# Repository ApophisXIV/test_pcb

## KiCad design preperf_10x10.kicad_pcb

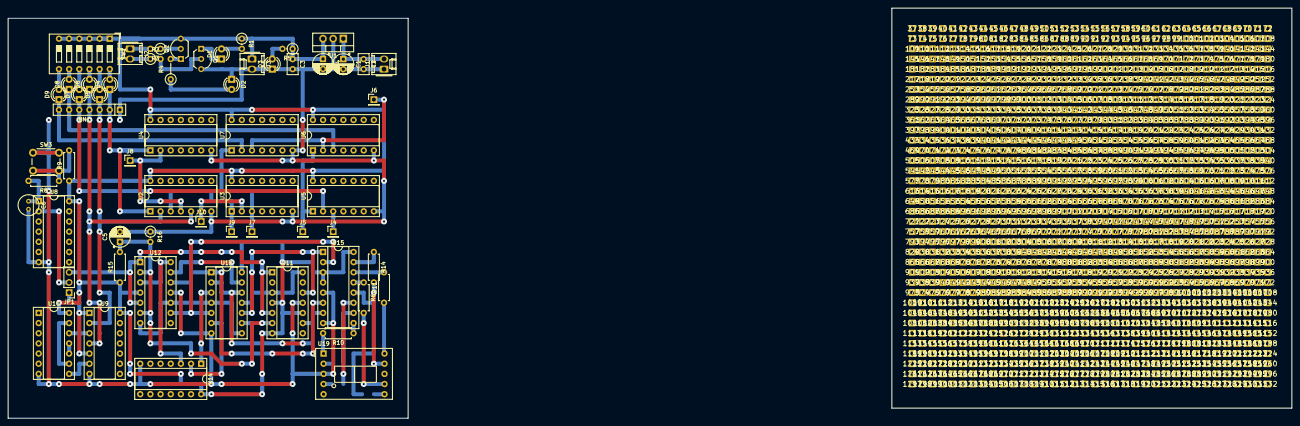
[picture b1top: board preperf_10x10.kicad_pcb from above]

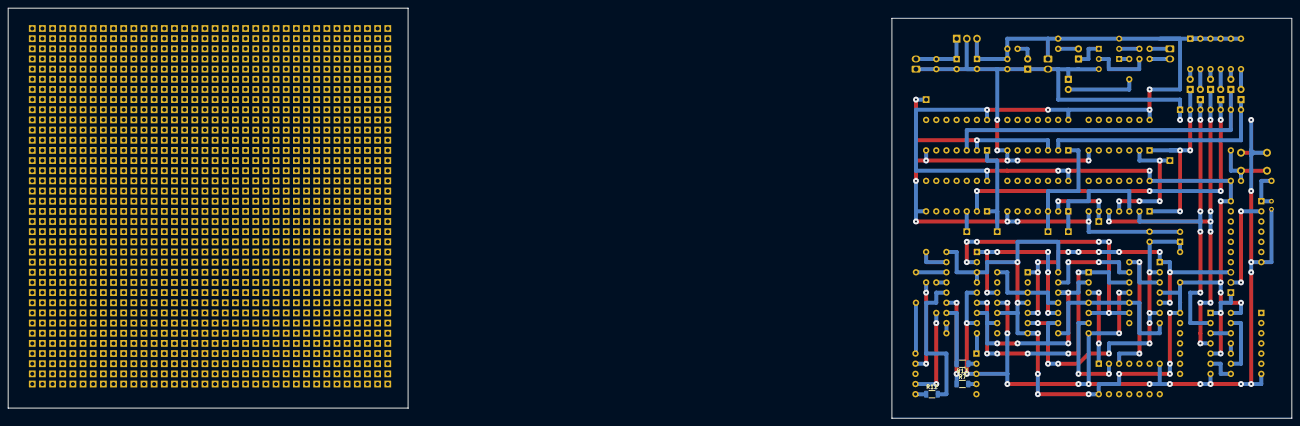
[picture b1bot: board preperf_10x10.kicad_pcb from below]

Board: 4 copper layers, 321.0 x 102.5 mm, 1359 parts (3 on the bottom side), 65 nets.

Parts:
37, 38, 39, 40, 41, 42, 43, 44, 45, 46, 47, 48, 49, 50, 51, 52, 53, 54, 55, 56, 57, 58, 59, 60, 61, 62, 63, 64, 65, 66, 67, 68, 69, 70, 71, 72, 73, 74, 75, 76, 77, 78, 79, 80, 81, 82, 83, 84, 85, 86, 87, 88, 89, 90, 91, 92, 93, 94, 95, 96, 97, 98, 99, 100, 101, 102, 103, 104, 105, 106, 107, 108, 109, 110, 111, 112, 113, 114, 115, 116, 117, 118, 119, 120, 121, 122, 123, 124, 125, 126, 127, 128, 129, 130, 131, 132, 133, 134, 135, 136, 137, 138, 139, 140, 141, 142, 143, 144, 145, 146, 147, 148, 149, 150, 151, 152, 153, 154, 155, 156, 157, 158, 159, 160, 161, 162, 163, 164, 165, 166, 167, 168, 169, 170, 171, 172, 173, 174, 175, 176, 177, 178, 179, 180, 181, 182, 183, 184, 185, 186, 187, 188, 189, 190, 191, 192, 193, 194, 195, 196, 197, 198, 199, 200, 201, 202, 203, 204, 205, 206, 207, 208, 209, 210, 211, 212, 213, 214, 215, 216, 217, 218, 219, 220, 221, 222, 223, 224, 225, 226, 227, 228, 229, 230, 231, 232, 233, 234, 235, 236, 237, 238, 239, 240, 241, 242, 243, 244, 245, 246, 247, 248, 249, 250, 251, 252, 253, 254, 255, 256, 257, 258, 259, 260, 261, 262, 263, 264, 265, 266, 267, 268, 269, 270, 271, 272, 273, 274, 275, 276, 277, 278, 279, 280, 281, 282, 283, 284, 285, 286, 287, 288, 289, 290, 291, 292, 293, 294, 295, 296, 297, 298, 299, 300, 301, 302, 303, 304, 305, 306, 307, 308, 309, 310, 311, 312, 313, 314, 315, 316, 317, 318, 319, 320, 321, 322, 323, 324, 325, 326, 327, 328, 329, 330, 331, 332, 333, 334, 335, 336, 337, 338, 339, 340, 341, 342, 343, 344, 345, 346, 347, 348, 349, 350, 351, 352, 353, 354, 355, 356, 357, 358, 359, 360, 361, 362, 363, 364, 365, 366, 367, 368, 369, 370, 371, 372, 373, 374, 375, 376, 377, 378, 379, 380, 381, 382, 383, 384, 385, 386, 387, 388, 389, 390, 391, 392, 393, 394, 395, 396, 397, 398, 399, 400, 401, 402, 403, 404, 405, 406, 407, 408, 409, 410, 411, 412, 413, 414, 415, 416, 417, 418, 419, 420, 421, 422, 423, 424, 425, 426, 427, 428, 429, 430, 431, 432, 433, 434, 435, 436, 437, 438, 439, 440, 441, 442, 443, 444, 445, 446, 447, 448, 449, 450, 451, 452, 453, 454, 455, 456, 457, 458, 459, 460, 461, 462, 463, 464, 465, 466, 467, 468, 469, 470, 471, 472, 473, 474, 475, 476, 477, 478, 479, 480, 481, 482, 483, 484, 485, 486, 487, 488, 489, 490, 491, 492, 493, 494, 495, 496, 497, 498, 499, 500, 501, 502, 503, 504, 505, 506, 507, 508, 509, 510, 511, 512, 513, 514, 515, 516, 517, 518, 519, 520, 521, 522, 523, 524, 525, 526, 527, 528, 529, 530, 531, 532, 533, 534, 535, 536, 537, 538, 539, 540, 541, 542, 543, 544, 545, 546, 547, 548, 549, 550, 551, 552, 553, 554, 555, 556, 557, 558, 559, 560, 561, 562, 563, 564, 565, 566, 567, 568, 569, 570, 571, 572, 573, 574, 575, 576, 577, 578, 579, 580, 581, 582, 583, 584, 585, 586, 587, 588, 589, 590, 591, 592, 593, 594, 595, 596, 597, 598, 599, 600, 601, 602, 603, 604, 605, 606, 607, 608, 609, 610, 611, 612, 613, 614, 615, 616, 617, 618, 619, 620, 621, 622, 623, 624, 625, 626, 627, 628, 629, 630, 631, 632, 633, 634, 635, 636, 637, 638, 639, 640, 641, 642, 643, 644, 645, 646, 647, 648, 649, 650, 651, 652, 653, 654, 655, 656, 657, 658, 659, 660, 661, 662, 663, 664, 665, 666, 667, 668, 669, 670, 671, 672, 673, 674, 675, 676, 677, 678, 679, 680, 681, 682, 683, 684, 685, 686, 687, 688, 689, 690, 691, 692, 693, 694, 695, 696, 697, 698, 699, 700, 701, 702, 703, 704, 705, 706, 707, 708, 709, 710, 711, 712, 713, 714, 715, 716, 717, 718, 719, 720, 721, 722, 723, 724, 725, 726, 727, 728, 729, 730, 731, 732, 733, 734, 735, 736, 737, 738, 739, 740, 741, 742, 743, 744, 745, 746, 747, 748, 749, 750, 751, 752, 753, 754, 755, 756, 757, 758, 759, 760, 761, 762, 763, 764, 765, 766, 767, 768, 769, 770, 771, 772, 773, 774, 775, 776, 777, 778, 779, 780, 781, 782, 783, 784, 785, 786, 787, 788, 789, 790, 791, 792, 793, 794, 795, 796, 797, 798, 799, 800, 801, 802, 803, 804, 805, 806, 807, 808, 809, 810, 811, 812, 813, 814, 815, 816, 817, 818, 819, 820, 821, 822, 823, 824, 825, 826, 827, 828, 829, 830, 831, 832, 833, 834, 835, 836, 837, 838, 839, 840, 841, 842, 843, 844, 845, 846, 847, 848, 849, 850, 851, 852, 853, 854, 855, 856, 857, 858, 859, 860, 861, 862, 863, 864, 865, 866, 867, 868, 869, 870, 871, 872, 873, 874, 875, 876, 877, 878, 879, 880, 881, 882, 883, 884, 885, 886, 887, 888, 889, 890, 891, 892, 893, 894, 895, 896, 897, 898, 899, 900, 901, 902, 903, 904, 905, 906, 907, 908, 909, 910, 911, 912, 913, 914, 915, 916, 917, 918, 919, 920, 921, 922, 923, 924, 925, 926, 927, 928, 929, 930, 931, 932, 933, 934, 935, 936, 937, 938, 939, 940, 941, 942, 943, 944, 945, 946, 947, 948, 949, 950, 951, 952, 953, 954, 955, 956, 957, 958, 959, 960, 961, 962, 963, 964, 965, 966, 967, 968, 969, 970, 971, 972, 973, 974, 975, 976, 977, 978, 979, 980, 981, 982, 983, 984, 985, 986, 987, 988, 989, 990, 991, 992, 993, 994, 995, 996, 997, 998, 999, 1000, 1001, 1002, 1003, 1004, 1005, 1006, 1007, 1008, 1009, 1010, 1011, 1012, 1013, 1014, 1015, 1016, 1017, 1018, 1019, 1020, 1021, 1022, 1023, 1024, 1025, 1026, 1027, 1028, 1029, 1030, 1031, 1032, 1033, 1034, 1035, 1036, 1037, 1038, 1039, 1040, 1041, 1042, 1043, 1044, 1045, 1046, 1047, 1048, 1049, 1050, 1051, 1052, 1053, 1054, 1055, 1056, 1057, 1058, 1059, 1060, 1061, 1062, 1063, 1064, 1065, 1066, 1067, 1068, 1069, 1070, 1071, 1072, 1073, 1074, 1075, 1076, 1077, 1078, 1079, 1080, 1081, 1082, 1083, 1084, 1085, 1086, 1087, 1088, 1089, 1090, 1091, 1092, 1093, 1094, 1095, 1096, 1097, 1098, 1099, 1100, 1101, 1102, 1103, 1104, 1105, 1106, 1107, 1108, 1109, 1110, 1111, 1112, 1113, 1114, 1115, 1116, 1117, 1118, 1119, 1120, 1121, 1122, 1123, 1124, 1125, 1126, 1127, 1128, 1129, 1130, 1131, 1132, 1133, 1134, 1135, 1136, 1137, 1138, 1139, 1140, 1141, 1142, 1143, 1144, 1145, 1146, 1147, 1148, 1149, 1150, 1151, 1152, 1153, 1154, 1155, 1156, 1157, 1158, 1159, 1160, 1161, 1162, 1163, 1164, 1165, 1166, 1167, 1168, 1169, 1170, 1171, 1172, 1173, 1174, 1175, 1176, 1177, 1178, 1179, 1180, 1181, 1182, 1183, 1184, 1185, 1186, 1187, 1188, 1189, 1190, 1191, 1192, 1193, 1194, 1195, 1196, 1197, 1198, 1199, 1200, 1201, 1202, 1203, 1204, 1205, 1206, 1207, 1208, 1209, 1210, 1211, 1212, 1213, 1214, 1215, 1216, 1217, 1218, 1219, 1220, 1221, 1222, 1223, 1224, 1225, 1226, 1227, 1228, 1229, 1230, 1231, 1232, 1233, 1234, 1235, 1236, 1237, 1238, 1239, 1240, 1241, 1242, 1243, 1244, 1245, 1246, 1247, 1248, 1249, 1250, 1251, 1252, 1253, 1254, 1255, 1256, 1257, 1258, 1259, 1260, 1261, 1262, 1263, 1264, 1265, 1266, 1267, 1268, 1269, 1270, 1271, 1272, 1273, 1274, 1275, 1276, 1277, 1278, 1279, 1280, 1281, 1282, 1283, 1284, 1285, 1286, 1287, 1288, 1289, 1290, 1291, 1292, 1293, 1294, 1295, 1296, 1297, 1298, 1299, 1300, 1301, 1302, 1303, 1304, 1305, 1306, 1307, 1308, 1309, 1310, 1311, 1312, 1313, 1314, 1315, 1316, 1317, 1318, 1319, 1320, 1321, 1322, 1323, 1324, 1325, 1326, 1327, 1328, 1329, 1330, 1331, 1332: (no value)
C1, C4: C_Polarized_US; CP_Radial_D5.0mm_P2.50mm
C2, C3: C; C_Disc_D5.0mm_W2.5mm_P2.50mm
C5: C_Small; CP_Radial_D5.0mm_P2.50mm
C6: C; C_Radial_D5.0mm_H5.0mm_P2.00mm
D1, D2, D3, D4, D5, D6, D7, D8: LED; LED_D3.0mm
D9: LED; LED_D3.0mm_FlatTop
J1, J2, J3: Conn_01x02_Pin; Molex_KK-254_AE-6410-02A_1x02_P2.54mm_Vertical
J4, J5, J6, J7, J8, J9, J10: Conn_01x01_Pin; PinHeader_1x01_P2.54mm_Vertical
JP1: Jumper_3_Bridged12; PinHeader_1x03_P2.54mm_Vertical
Q1: BC548; TO-92_Inline_Wide
Q2: BC558; TO-92_Inline_Wide
R1, R2, R3, R5, R16: R_US; R_Axial_DIN0207_L6.3mm_D2.5mm_P2.54mm_Vertical
R4: R_US; R_Axial_DIN0207_L6.3mm_D2.5mm_P5.08mm_Vertical
R6, R8, R9, R10, R11, R14, R15: R_US; R_Axial_DIN0207_L6.3mm_D2.5mm_P7.62mm_Horizontal
R7, R12, R13: R_US; R_1206_3216Metric
RN1: R_Network06; R_Array_SIP7
SW1: SW_DIP_x06; SW_DIP_SPSTx06_Slide_9.78x17.42mm_W7.62mm_P2.54mm
SW3: SW_Push; SW_PUSH_6mm_H4.3mm
U1: LM7805_TO220; TO-220-3_Vertical
U2, U9, U13: 74LS08; DIP-14_W7.62mm_Socket
U3, U14: 74LS32; DIP-14_W7.62mm_Socket
U4: 74LS04; DIP-14_W7.62mm_Socket
U5: 74LS386; DIP-14_W7.62mm_Socket
U6, U10: 74LS02; DIP-14_W7.62mm_Socket
U7: 7400; DIP-14_W7.62mm_Socket
U8: 74LS14; DIP-14_W7.62mm_Socket
U11, U12: 74LS73; DIP-14_W7.62mm_Socket
U15: 4511; DIP-16_W7.62mm_Socket
U19: D168K; D1X8K

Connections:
+5V: C3.1, C4.1, J3.1, Q2.3 (E), R1.1, R5.1, R9.1, R15.1, SW1.1, SW1.2, SW1.3, SW1.4, SW1.5, SW1.6, U1.3 (VO), U2.14 (VCC), U3.14 (VCC), U4.14 (VCC), U5.14 (VCC), U6.14 (VCC), U7.14 (VCC), U8.14 (VCC), U9.14 (VCC), U10.14 (VCC), U11.4 (VCC), U11.7 (J), U11.10 (K), U12.4 (VCC), U13.14 (VCC), U14.14 (VCC), U15.3 (~LT), U15.4 (~BI), U15.16 (Vdd)
/Boton antirebote - Latch SR/CLK: JP1.1 (A), U9.1, U9.5
/Boton antirebote - Latch SR/Q: U10.10, U10.11
/Boton antirebote - Latch SR/~Q: U10.9, U10.13
/Contador BCD/A: U11.9 (Q), U13.2, U13.9, U13.12, U15.7 (DA)
/Contador BCD/B: U11.12 (Q), U13.10, U15.1 (DB)
/Contador BCD/C: U12.9 (Q), U13.5, U15.2 (DC)
/Contador BCD/CLK: JP1.3 (B), U11.1 (C), U11.5 (C), U12.1 (C), U12.5 (C)
/Contador BCD/D: U12.12 (Q), U13.1, U15.6 (DD)
/Contador BCD/POR: C5.1, R15.2, R16.2, U11.2 (~R), U11.6 (~R), U12.2 (~R), U12.6 (~R)
/Logic/A: D4.1 (K), RN1.2 (R1), U2.1, U4.1
/Logic/B: D5.1 (K), RN1.3 (R2), U2.2, U9.2
/Logic/C: D6.1 (K), RN1.4 (R3), U2.5, U9.4
/Logic/D: D7.1 (K), RN1.5 (R4), U5.2
/Logic/E: D8.1 (K), RN1.6 (R5), U6.3
/Logic/F: D9.1 (K), RN1.7 (R6), U7.2
/PSU 5V 1A/VIN: C1.1, C2.1, J1.2, U1.1 (VI)
/Punta Logica/HIGH_LVL: J2.2, R2.1
/Punta Logica/LOW_LVL: J2.1, R3.2
GND: C1.2, C2.2, C3.2, C4.2, C5.2, C6.2, D2.1 (K), D3.1 (K), J1.1, J3.2, Q1.3 (E), R16.1, RN1.1 (common), SW3.1, U1.2 (GND), U2.7 (GND), U3.7 (GND), U4.7 (GND), U5.7 (GND), U6.7 (GND), U7.7 (GND), U8.7 (GND), U9.7 (GND), U10.7 (GND), U11.11 (GND), U12.11 (GND), U13.7 (GND), U14.7 (GND), U15.5 (~EL), U15.8 (Vss), U19.3 (CC)
unnamed: C6.1, R8.2, U8.1
unnamed: D1.2 (A), R1.2
unnamed: D1.1 (K), Q1.1 (C)
unnamed: D2.2 (A), R4.1
unnamed: D3.2 (A), R5.2
unnamed: D4.2 (A), SW1.12
unnamed: D5.2 (A), SW1.11
unnamed: D6.2 (A), SW1.10
unnamed: D7.2 (A), SW1.9
unnamed: D8.2 (A), SW1.8
unnamed: D9.2 (A), SW1.7
unnamed: J4.1, U5.3
unnamed: J5.1, U5.1, U6.1
unnamed: J6.1, U6.2, U7.3
unnamed: J7.1, U3.3, U7.1
unnamed: J8.1, U2.4, U4.2
unnamed: J9.1, U2.3, U3.1
unnamed: J10.1, U2.6, U3.2
unnamed: JP1.2 (C), U8.2
unnamed: Q1.2 (B), R2.2
unnamed: Q2.2 (B), R3.1
unnamed: Q2.1 (C), R4.2
unnamed: R8.1, R9.2, SW3.2
unnamed: U9.6, U10.8
unnamed: U9.3, U10.12
unnamed: U11.3 (K), U11.14 (J), U13.11
unnamed: U12.7 (J), U12.10 (K), U13.4, U13.8
unnamed: U12.3 (K), U12.14 (J), U14.3
unnamed: U12.13 (~Q), U13.13
unnamed: U13.3, U14.1
unnamed: U13.6, U14.2
unnamed: R6.1, U15.13 (Qa)
unnamed: R12.2, U15.12 (Qb)
unnamed: R7.1, U15.11 (Qc)
unnamed: R13.2, U15.10 (Qd)
unnamed: R10.1, U15.9 (Qe)
unnamed: R14.1, U15.15 (Qf)
unnamed: R11.2, U15.14 (Qg)
unnamed: R6.2, U19.7 (A)
unnamed: R12.1, U19.6 (B)
unnamed: R7.2, U19.4 (C)
unnamed: R13.1, U19.2 (D)
unnamed: R10.2, U19.1 (E)
unnamed: R14.2, U19.9 (F)
unnamed: R11.1, U19.10 (G)
